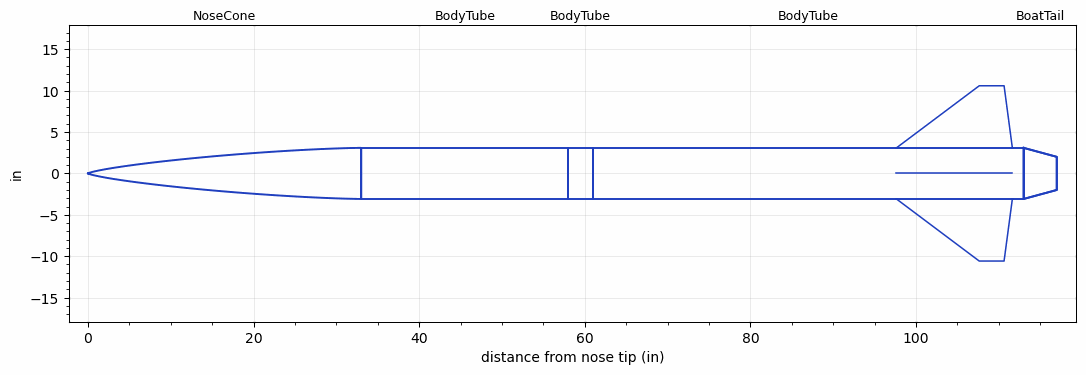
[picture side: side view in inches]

<RASAeroDocument>
 <FileVersion>2</FileVersion>
 <RocketDesign>
  <NoseCone>
   <Length>32.9999</Length>
   <Diameter>6.17</Diameter>
   <Shape>Von Karman Ogive</Shape>
   <Location>0</Location>
  </NoseCone>
  <BodyTube>
   <Length>24.9999</Length>
   <Diameter>6.17</Diameter>
   <Location>32.9999</Location>
  </BodyTube>
  <BodyTube>
   <Length>3</Length>
   <Diameter>6.17</Diameter>
   <Location>57.9999</Location>
  </BodyTube>
  <BodyTube>
   <Length>51.9999</Length>
   <Diameter>6.17</Diameter>
   <RailGuideDiameter>0.49</RailGuideDiameter>
   <RailGuideHeight>0.56</RailGuideHeight>
   <Location>60.9999</Location>
   <BoattailLength>4</BoattailLength>
   <BoattailRearDiameter>4</BoattailRearDiameter>
   <Fin>
    <Count>4</Count>
    <Chord>14</Chord>
    <Span>7.5</Span>
    <SweepDistance>10</SweepDistance>
    <TipChord>3</TipChord>
    <Thickness>0.2</Thickness>
    <Location>15.365</Location>
    <AirfoilSection>Rounded</AirfoilSection>
   </Fin>
  </BodyTube>
  <BoatTail>
   <Length>4</Length>
   <Diameter>6.17</Diameter>
   <RearDiameter>4</RearDiameter>
   <Location>112.9998</Location>
  </BoatTail>
  <Surface>Polished</Surface>
  <ModifiedBarrowman>False</ModifiedBarrowman>
  <Turbulence>False</Turbulence>
  <UseBooster1>False</UseBooster1>
  <UseBooster2>False</UseBooster2>
 </RocketDesign>
 <LaunchSite>
  <Altitude>0</Altitude>
  <Pressure>29.9214</Pressure>
  <RodAngle>0</RodAngle>
  <RodLength>10</RodLength>
  <Temperature>59</Temperature>
  <WindSpeed>4.4739</WindSpeed>
 </LaunchSite>
 <Recovery>
  <Altitude1>656.168</Altitude1>
  <Altitude2>600</Altitude2>
  <DeviceType1>Parachute</DeviceType1>
  <DeviceType2>Parachute</DeviceType2>
  <Event1>True</Event1>
  <Event2>True</Event2>
  <Size1>24</Size1>
  <Size2>119.9998</Size2>
  <EventType1>Apogee</EventType1>
  <EventType2>Altitude</EventType2>
  <CD1>2.2</CD1>
  <CD2>0</CD2>
 </Recovery>
 <SimulationList>
  <Simulation>
   <SustainerEngine>M2000R  (AT)</SustainerEngine>
   <SustainerLaunchWt>64.2398</SustainerLaunchWt>
   <SustainerCG>74.8708</SustainerCG>
   <SustainerIgnitionDelay>0</SustainerIgnitionDelay>
   <Booster1SeparationDelay>0</Booster1SeparationDelay>
   <Booster1IgnitionDelay>0</Booster1IgnitionDelay>
   <IncludeBooster1>False</IncludeBooster1>
   <Booster2Delay>0</Booster2Delay>
   <IncludeBooster2>False</IncludeBooster2>
   <TimetoApogee>25.78049</TimetoApogee>
   <MaxAltitude>10538.08</MaxAltitude>
   <MaxVelocity>922.4242</MaxVelocity>
  </Simulation>
  <Simulation>
   <SustainerEngine>M2500T  (AT)</SustainerEngine>
   <SustainerLaunchWt>62.2052</SustainerLaunchWt>
   <SustainerCG>73.9881</SustainerCG>
   <SustainerIgnitionDelay>0</SustainerIgnitionDelay>
   <Booster1SeparationDelay>0</Booster1SeparationDelay>
   <Booster1IgnitionDelay>0</Booster1IgnitionDelay>
   <IncludeBooster1>False</IncludeBooster1>
   <Booster2Delay>0</Booster2Delay>
   <IncludeBooster2>False</IncludeBooster2>
   <TimetoApogee>26.1305</TimetoApogee>
   <MaxAltitude>11422.4</MaxAltitude>
   <MaxVelocity>1007.289</MaxVelocity>
  </Simulation>
  <Simulation>
   <SustainerEngine>M1939W  (AT)</SustainerEngine>
   <SustainerLaunchWt>64.2428</SustainerLaunchWt>
   <SustainerCG>74.8719</SustainerCG>
   <SustainerIgnitionDelay>0</SustainerIgnitionDelay>
   <Booster1SeparationDelay>0</Booster1SeparationDelay>
   <Booster1IgnitionDelay>0</Booster1IgnitionDelay>
   <IncludeBooster1>False</IncludeBooster1>
   <Booster2Delay>0</Booster2Delay>
   <IncludeBooster2>False</IncludeBooster2>
   <TimetoApogee>27.92054</TimetoApogee>
   <MaxAltitude>12356.49</MaxAltitude>
   <MaxVelocity>959.3519</MaxVelocity>
  </Simulation>
  <Simulation>
   <SustainerEngine>M750W  (AT)</SustainerEngine>
   <SustainerLaunchWt>63.7749</SustainerLaunchWt>
   <SustainerCG>74.6979</SustainerCG>
   <SustainerIgnitionDelay>0</SustainerIgnitionDelay>
   <Booster1SeparationDelay>0</Booster1SeparationDelay>
   <Booster1IgnitionDelay>0</Booster1IgnitionDelay>
   <IncludeBooster1>False</IncludeBooster1>
   <Booster2Delay>0</Booster2Delay>
   <IncludeBooster2>False</IncludeBooster2>
  </Simulation>
  <Simulation>
   <SustainerEngine>M2400T  (AT)</SustainerEngine>
   <SustainerLaunchWt>58.6496</SustainerLaunchWt>
   <SustainerCG>73.2544</SustainerCG>
   <SustainerIgnitionDelay>0</SustainerIgnitionDelay>
   <Booster1SeparationDelay>0</Booster1SeparationDelay>
   <Booster1IgnitionDelay>0</Booster1IgnitionDelay>
   <IncludeBooster1>False</IncludeBooster1>
   <Booster2Delay>0</Booster2Delay>
   <IncludeBooster2>False</IncludeBooster2>
  </Simulation>
  <Simulation>
   <SustainerLaunchWt>59.1584</SustainerLaunchWt>
   <SustainerCG>73.4951</SustainerCG>
   <SustainerIgnitionDelay>0</SustainerIgnitionDelay>
   <Booster1SeparationDelay>0</Booster1SeparationDelay>
   <Booster1IgnitionDelay>0</Booster1IgnitionDelay>
   <IncludeBooster1>False</IncludeBooster1>
   <Booster2Delay>0</Booster2Delay>
   <IncludeBooster2>False</IncludeBooster2>
  </Simulation>
 </SimulationList>
</RASAeroDocument>
